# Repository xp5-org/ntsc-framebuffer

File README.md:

NTSC framebuffer built around 74x cmos logic gates and an 128k x 8bit sram module 

** this is incomplete and not yet built, in-progress **

- 8 bits for color + brightness
- 17 bits address
- transfer data in during vblank period

Tasks remaining:
  - complete memory addressing circuitry
  - check gate timings for brightness & color control paths
  - place adjustment potentiometers for setting PNP transistor bias
  - distribute ceramic capacitors
  - add debug testpads onto pcb

# Table of Contents
- [Current PCB Layout](#current-pcb-layout)
- [H&V Counter](#hvcounter)
- [HRESET](#hreset)
- [VRESET](#vreset)
- [HBLANK](#hblank-hsync)
- [VBLANK](#vblank-vsync)
- [COLORBURST](#colorburst)
- [COLORSELECT](#colorselect)
- [BRIGHTNESS](#brightness)
- [MEMORYANDBUS](#memoryandbus)
- [Output Amplifier](#outputamp)
- [Components selection](#components)
- [Simulating](#simtools)

# Current PCB Layout

<br>

<br><br><br><br><br><br><br><br> 

# hvcounter
This is the core of the circuit, its two 4040 counters, one driving the other. the first counts out 454 which is the number of inactive + active horizontal pixels per row. the output is binary, and with enough AND gates alongside numerous D type flipflops, specific events can be timed out and set to form the sync timings needed

<br><br><br><br><br><br><br><br> 

# HRESET

256 + 128 + 64 + 4 + 2
counts out 454 horizontal & sets HRESET flag to high 5V
and on the next clock pulse from not the timer we are resetting but the actual clock source

<br><br><br><br><br><br><br><br> 

# VRESET

vreset is 1V + 4V + 256V for 261 vertical lines before resetting the counter

vertical reset is checked at the end of the horizontal scanline, so we use _HRESET as the clock for vreset - the condition of 261V lines is set only when _HRESET is ready

# HBLANK-HSYNC

the circuit starts off with some DC bias to give a sync tip from the "previous" scanline, and then at H2 + H8 HBLANK-ENABLE flop is cycled on. When this is on, elsewhere in the circuit the bias is cut off and gives us the horizontal sync tip

When H2 + H8 + H32 is seen (H42) , HBLANK_DISABLE is turned on, which is a 2nd flop "HSYNC B"

this lets me chain the hsync events together with explicit start and stop events, block them from re-triggering

<br><br><br><br><br><br><br><br> 

# VBLANK-VSYNC

<br><br><br><br><br><br><br><br> 

# COLORBURST

<br><br><br><br><br><br><br><br> 

# COLORSELECT

the 4-16 mux is often used for memory addressing and is only available in active-low, so in this case im using NOR gates to invert the signal . the MUX outputs are always high-inactive, so all NOR gates except for the active one are getting a positive voltage which turns them all off, exxcept for the active-low received from the MUX, this NOR gate switches on and provides a color clock at specific delays introduced by the 74AHC451's 4-5ns gate propigation delay
<br><br><br><br><br><br><br><br> 

# BRIGHTNESS

<br><br><br><br><br><br><br><br> 

# MEMORYANDBUS

<br><br><br><br><br><br><br><br> 

# outputamp
The output-amplifier interfaces the low-current, low impedience CMOS or TTL logic with the 1.4v, 75-ohm composite. 

HSYNC, Colorburst, and Pixel Input are given to the amplifiers input. Its first passed through a 2n7000 N-channel mosfet which inverts the signal. This drives a PNP transistor to return it back to positive output, this allowed the GND of the composite-out to also be the same reference plane as the GND of this circuit (pnp could be omitted and use only mosfet with resistor network and floating Gnd)

This has two additional mosfets for saturation bias and output voltage reduction (brightness).  The saturation mosfet biases the PNPs turnoff point "upwards" so that its off point rises above what hsync/hblank would have been . this serves the purpose of adding DC bias to reduce the modulation of the output without affecting the output peak (overall brightness). in summary, this is an amplifier which can control the height of the bottoms and tops of the wave output separately. its needed for color, but could dispose of half the mosfets if it were used for monochrome

<br><br><br><br><br><br><br><br> 

# Components
- 74HC74 D-FLOP
- 74HC08 AND
- 74HC02 NOR
- 74hc244 buffers
- 74hc154 4-to-16 mux
- 74ahc541 inv buffers (color delay line)
- CD4040 12 bit counter
- 14.318mhz crystal
- 128x8 sram HM628128DLP-5
- 2n5087 pnp or equivalent
- 2n7000 mosfet
- 7805 regulator

<br><br><br><br><br><br><br><br> 

# simtools

[LTSpice Model of Output Amplifier](./ltspice_sim/video_output_amplifier.asc)

[Digital Logic simulation](./Digital_sim/ntsc_gen.dig)

output amplifier in ltspice, showing peak brightness vs minimum brightness pixels , there is some distortion in the sim. Some gates are switching on/off before others and causing brief voltage spikes, this might be ignorable on the physical circuit ill have to go through the circuit flow to see what the issue is

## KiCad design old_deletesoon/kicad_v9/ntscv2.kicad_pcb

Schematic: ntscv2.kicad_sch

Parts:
C1, C4, C5, C6, C7, C8, C9, C10, C11, C12, C13, C14, C15, C16, C17, C18, C19, C20, C21, C22, C23, C24, C25, C27: C; C_Disc_D5.1mm_W3.2mm_P5.00mm
C2, C3: 10pF; C_Disc_D3.0mm_W2.0mm_P2.50mm
C26: C; C_Radial_D8.0mm_H7.0mm_P3.50mm
D1, D2, D3, D4, D5: 1N4448; D_DO-35_SOD27_P7.62mm_Horizontal
D6, D7, D8, D9, D10, D11, D12, D13, D14, D15, D16, D17, D18, D19, D20, D21, D22, D23, D24, D25, D26, D27, D28, D29, D30, D31, D32, D33, D34, D35, D36: 1N4148; D_DO-35_SOD27_P7.62mm_Horizontal
J1: Conn_Coaxial; BNC_TEConnectivity_1478035_Horizontal
J2: Conn_02x04_Counter_Clockwise; PinSocket_2x04_P2.54mm_Vertical
J3: Conn_02x20_Counter_Clockwise; PinSocket_2x20_P2.54mm_Vertical
Q1: BC327; TO-92_Inline
Q2, Q3, Q4: 2N7000; TO-92_Inline
R1, R3, R4, R5, R6, R7, R8, R9, R10, R11, R12, R13, R14, R15, R16, R17, R18, R19, R20, R21, R22, R23, R24, R25, R26, R27, R28, R29, R30: R; R_Axial_DIN0204_L3.6mm_D1.6mm_P5.08mm_Horizontal
R2: 680; R_Axial_DIN0204_L3.6mm_D1.6mm_P7.62mm_Horizontal
R31, R32, R33: 50R; R_Axial_DIN0204_L3.6mm_D1.6mm_P5.08mm_Horizontal
U1, U2, U3, U4, U5, U40: 74HCT74; SO-14_3.9x8.65mm_P1.27mm
U6, U7, U14, U15: 4040; DIP-16_W7.62mm_SMDSocket_SmallPads
U8: 74HC7014; SOIC-14_3.9x8.7mm_P1.27mm
U9, U10, U11, U13: 4081; DIP-14_W7.62mm
U12: 4081; SO-14_3.9x8.65mm_P1.27mm
U16, U30: 74154; SOIC-24W_7.5x15.4mm_P1.27mm
U17, U18, U21: 74AHC541; SOIC-20W_7.5x12.8mm_P1.27mm
U19, U20, U22, U23: 74HC02; SOIC-14_3.9x8.7mm_P1.27mm
U24, U25, U26, U27, U28, U29, U31, U32: 74HC244; SSOP-20_4.4x6.5mm_P0.65mm
U33: HM628128ALFP-5; DIP-32_W15.24mm; PARTREV 20/6/13
U34, U35: 74HC540D_653; SOIC-20W_7.5x12.8mm_P1.27mm; MPN 74HC540D,653
U46: LM7805_TO220; TO-220-3_Vertical
Y1: Crystal; Crystal_HC49-U_Vertical

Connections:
1H: U6.9 (Q0), U17.2 (A0), U19.2
1V: U7.9 (Q0), U10.1
2H: U6.7 (Q1), U9.1
2V: U7.7 (Q1)
4H: U6.6 (Q2), U9.2
4V: U7.6 (Q2), U10.5
5vdc: C1.1, C4.1, C5.1, C6.1, C7.1, C8.1, C9.1, C10.1, C11.1, C12.1, C13.1, C14.1, C15.1, C16.1, C17.1, C18.1, C19.1, C20.1, C21.1, C22.1, C23.1, C24.1, C25.1, C26.1, J2.1, J2.2, Q1.1 (C), R12.1, U1.10 (~S), U1.13 (~R), U1.14 (VCC), U2.10 (~S), U2.13 (~R), U2.14 (VCC), U3.2 (D), U3.4 (~S), U3.10 (~S), U3.12 (D), U3.14 (VCC), U4.2 (D), U4.4 (~S), U4.10 (~S), U4.12 (D), U4.14 (VCC), U5.2 (D), U5.4 (~S), U5.10 (~S), U5.12 (D), U5.14 (VCC), U6.16 (VDD), U7.16 (VDD), U8.14 (VCC), U9.14 (VDD), U10.14 (VDD), U11.14 (VDD), U12.14 (VDD), U13.14 (VDD), U14.16 (VDD), U15.16 (VDD), U16.24 (VCC), U17.20 (VCC), U18.20 (VCC), U19.14 (VCC), U20.14 (VCC), U21.20 (VCC), U22.14 (VCC), U23.14 (VCC), U24.20 (VCC), U25.20 (VCC), U26.20 (VCC), U27.20 (VCC), U28.20 (VCC), U29.20 (VCC), U30.24 (VCC), U31.20 (VCC), U32.20 (VCC), U33.32 (VCC), U34.20 (VCC), U35.20 (VCC), U40.1 (~R), U40.4 (~S), U40.10 (~S), U40.13 (~R), U40.14 (VCC), U46.3 (VO)
7.1mhz_CLK1: U1.5 (Q), U6.10 (CLK), U7.10 (CLK)
8H: U6.5 (Q3)
8V: U7.5 (Q3)
14mhz_CLK0: U1.3 (C), U2.3 (C), U8.6, U8.8, U8.10
16H: U6.3 (Q4)
16V: U7.3 (Q4)
32H: U6.2 (Q5)
32V: U7.2 (Q5)
64H: U6.4 (Q6), U9.5
64V: U7.4 (Q6)
128H: U6.13 (Q7), U9.6
128V: U7.13 (Q7)
256H: U6.12 (Q8), U9.13
256V: U7.12 (Q8), U10.6
512H: U6.14 (Q9)
512V: U7.14 (Q9)
BIAS_ADJ: J2.8, Q3.2 (G), R5.1
BRIGHTNESS: J2.7, Q4.2 (G), R6.1
CB_DISABLE: U5.9 (Q), U11.5
CB_ENABLE: U5.5 (Q), U12.8
CDL_output_enable: U16.18 (~E0), U16.19 (~E1), U17.1 (G1), U17.19 (G2), U18.1 (G1), U18.19 (G2), U21.1 (G1), U21.19 (G2), U30.18 (~E0), U30.19 (~E1), U34.1 (~OE), U34.19 (~OE2), U35.1 (~OE), U35.19 (~OE2)
FIELDCOUNTER: U40.2 (D), U40.6 (~Q)
GND: C1.2, C2.2, C3.2, C4.2, C5.2, C6.2, C7.2, C8.2, C9.2, C10.2, C11.2, C12.2, C13.2, C14.2, C15.2, C16.2, C17.2, C18.2, C19.2, C20.2, C21.2, C22.2, C23.2, C24.2, C25.2, C26.2, C27.2, J1.2 (Ext), J2.3, J2.4, J2.5, Q2.1 (S), Q3.1 (S), Q4.1 (S), R5.2, R6.2, R7.2, R11.2, R14.2, U1.7 (GND), U2.7 (GND), U3.7 (GND), U4.7 (GND), U5.7 (GND), U6.8 (VSS), U7.8 (VSS), U8.7 (GND), U9.7 (VSS), U10.7 (VSS), U11.7 (VSS), U12.7 (VSS), U13.7 (VSS), U14.8 (VSS), U15.8 (VSS), U16.12 (GND), U17.10 (GND), U18.10 (GND), U19.7 (GND), U20.7 (GND), U21.10 (GND), U22.7 (GND), U23.7 (GND), U24.10 (GND), U25.10 (GND), U26.10 (GND), U27.10 (GND), U28.10 (GND), U29.10 (GND), U30.12 (GND), U31.10 (GND), U32.10 (GND), U33.16 (VSS), U34.10 (GND), U35.10 (GND), U40.7 (GND), U46.2 (GND)
H2: U10.8, U11.12, U12.6
H4: U12.9
H8: U10.9, U11.6, U11.8
H16: U12.1
H32: U11.9, U12.2
H64: U12.13
HRESET: U2.5 (Q), U6.11 (Reset)
HSYNCA: U3.5 (Q)
HSYNCB: D2.2 (A), U3.9 (Q), U13.9
unnamed: C2.1, U8.1, Y1.1
unnamed: C3.1, R2.2, Y1.2
unnamed: D1.1 (K), U10.12
unnamed: D2.1 (K), U10.13
unnamed: D3.2 (A), U10.11
unnamed: D3.1 (K), R1.1
unnamed: D4.2 (A), U13.4
unnamed: D4.1 (K), R3.1
unnamed: D5.2 (A), U13.11
unnamed: D5.1 (K), R4.1
unnamed: D6.2 (A), U19.1
unnamed: D7.2 (A), U19.4
unnamed: D8.2 (A), U19.10
unnamed: D9.2 (A), U19.13
unnamed: D10.2 (A), U20.1
unnamed: D11.2 (A), U20.4
unnamed: D12.2 (A), U20.10
unnamed: D13.2 (A), U20.13
unnamed: D14.2 (A), U22.1
unnamed: D15.2 (A), U22.4
unnamed: D16.2 (A), U22.10
unnamed: D17.2 (A), U22.13
unnamed: D18.2 (A), U23.1
unnamed: D19.2 (A), U23.4
unnamed: D20.2 (A), U23.10
unnamed: D21.2 (A), R15.2
unnamed: D22.2 (A), R16.2
unnamed: D23.2 (A), R17.2
unnamed: D24.2 (A), R18.2
unnamed: D25.2 (A), R19.2
unnamed: D26.2 (A), R20.2
unnamed: D27.2 (A), R21.2
unnamed: D28.2 (A), R22.2
unnamed: D29.2 (A), R23.2
unnamed: D30.2 (A), R24.2
unnamed: D31.2 (A), R25.2
unnamed: D32.2 (A), R26.2
unnamed: D33.2 (A), R27.2
unnamed: D34.2 (A), R28.2
unnamed: D35.2 (A), R29.2
unnamed: D36.2 (A), R30.2
unnamed: Q1.2 (B), R9.2
unnamed: Q1.3 (E), R10.1
unnamed: Q2.3 (D), R8.2
unnamed: Q3.3 (D), R8.1, R9.1, R12.2, R14.1
unnamed: Q4.3 (D), R13.2
unnamed: R2.1, U8.2, U8.3
unnamed: U1.2 (D), U1.6 (~Q)
unnamed: U1.1 (~R), U1.4 (~S)
unnamed: U1.11 (C), U13.3
unnamed: U1.8 (~Q), U1.12 (D)
unnamed: U2.2 (D), U9.11
unnamed: U2.1 (~R), U2.4 (~S)
unnamed: U2.12 (D), U10.3
unnamed: U3.3 (C), U10.10
unnamed: U3.11 (C), U11.11
unnamed: U4.3 (C), U11.3
unnamed: U5.3 (C), U12.4
unnamed: U5.11 (C), U12.11
unnamed: U8.4, U8.5, U8.9, U8.11
unnamed: U9.3, U9.8
unnamed: U9.4, U9.9
unnamed: U9.10, U9.12
unnamed: U10.2, U10.4
unnamed: U11.2, U11.4
unnamed: U11.10, U11.13
unnamed: U12.3, U12.5
unnamed: U12.10, U12.12
unnamed: U13.10, U13.13
unnamed: U17.3 (A1), U17.18 (Y0)
unnamed: U17.4 (A2), U17.17 (Y1)
unnamed: U17.5 (A3), U17.16 (Y2)
unnamed: U17.6 (A4), U17.15 (Y3)
unnamed: U17.7 (A5), U17.14 (Y4)
unnamed: U17.8 (A6), U17.13 (Y5)
unnamed: U17.9 (A7), U17.12 (Y6)
unnamed: U17.11 (Y7), U18.9 (A7)
unnamed: U18.2 (A0), U18.17 (Y1)
unnamed: U18.3 (A1), U18.16 (Y2)
unnamed: U18.4 (A2), U18.15 (Y3)
unnamed: U18.5 (A3), U18.14 (Y4)
unnamed: U18.6 (A4), U18.13 (Y5)
unnamed: U18.7 (A5), U18.12 (Y6)
unnamed: U18.8 (A6), U18.11 (Y7)
unnamed: U18.18 (Y0), U21.2 (A0)
unnamed: U21.3 (A1), U21.18 (Y0)
unnamed: U21.4 (A2), U21.17 (Y1)
unnamed: U21.5 (A3), U21.16 (Y2)
unnamed: U21.6 (A4), U21.15 (Y3)
unnamed: U21.7 (A5), U21.14 (Y4)
unnamed: U21.8 (A6), U21.13 (Y5)
unnamed: U21.9 (A7), U21.12 (Y6)
unnamed: R15.1, U34.18 (~Y0)
unnamed: R19.1, U34.17 (~Y1)
unnamed: R23.1, U34.16 (~Y2)
unnamed: R27.1, U34.15 (~Y3)
unnamed: R16.1, U34.14 (~Y4)
unnamed: R20.1, U34.13 (~Y5)
unnamed: R24.1, U34.12 (~Y6)
unnamed: R28.1, U34.11 (~Y7)
unnamed: R17.1, U35.18 (~Y0)
unnamed: R21.1, U35.17 (~Y1)
unnamed: R25.1, U35.16 (~Y2)
unnamed: R29.1, U35.15 (~Y3)
unnamed: R18.1, U35.14 (~Y4)
unnamed: R22.1, U35.13 (~Y5)
unnamed: R26.1, U35.12 (~Y6)
unnamed: R30.1, U35.11 (~Y7)
unnamed: U40.5 (Q), U40.11 (C)
Output_Signal_75ohm: J1.1 (In), R10.2, R11.1, R13.1
PAGECOUNTER: U40.8 (~Q), U40.12 (D)
PIXELDRAWEN: U4.5 (Q), U13.6
PIXEL_INPUT_FROM_COLORARRAY: U13.5
V16: U4.11 (C)
VBLANK: R32.2, U4.9 (Q)
VRESET: U2.9 (Q), U7.11 (Reset), U14.11 (Reset), U15.11 (Reset), U40.3 (C)
_CB_DISABLE: U5.8 (~Q)
_CB_ENABLE: U5.6 (~Q)
_HRESET: U2.6 (~Q), U2.8 (~Q), U2.11 (C), U3.1 (~R), U3.13 (~R), U4.1 (~R), U5.1 (~R), U5.13 (~R)
_HSYNCA: D1.2 (A), U3.6 (~Q), U13.8
_HSYNCB: U3.8 (~Q)
_PIXELDRAWEN: U4.6 (~Q)
_VBLANK: R31.1, R33.2, U4.8 (~Q), U11.1, U13.2
_VRESET: U4.13 (~R)
ampinput: J2.6, Q2.2 (G), R1.2, R3.2, R4.2, R7.1
bus_addr0: J3.40, U29.11 (2A3)
bus_addr1: J3.39, U27.2 (1A0)
bus_addr2: J3.38, U27.4 (1A1)
bus_addr3: J3.37, U27.6 (1A2)
bus_addr4: J3.36, U27.8 (1A3)
bus_addr5: J3.35, U27.17 (2A0)
bus_addr6: J3.34, U27.15 (2A1)
bus_addr7: J3.33, U27.13 (2A2)
bus_addr8: J3.32, U27.11 (2A3)
bus_addr9: J3.31, U28.2 (1A0)
bus_addr10: J3.30, U28.4 (1A1)
bus_addr11: J3.29, U28.6 (1A2)
bus_addr12: J3.28, U28.8 (1A3)
bus_addr13: J3.27, U28.17 (2A0)
bus_addr14: J3.26, U28.15 (2A1)
bus_addr15: J3.25, U28.13 (2A2)
bus_addr16: J3.24, U28.11 (2A3)
bus_data0: J3.1, U31.2 (1A0)
bus_data1: J3.2, U31.4 (1A1)
bus_data2: J3.3, U31.6 (1A2)
bus_data3: J3.4, U31.8 (1A3)
bus_data4: J3.5, U31.17 (2A0)
bus_data5: J3.6, U31.15 (2A1)
bus_data6: J3.7, U31.13 (2A2)
bus_data7: J3.8, U31.11 (2A3)
bus_writeflag_9thbit: J3.9, R31.2, U13.1, U29.13 (2A2)
colorburst_delayline: D7.1 (K), D8.1 (K), D9.1 (K), D10.1 (K), D11.1 (K), D12.1 (K), D13.1 (K), D14.1 (K), D15.1 (K), D16.1 (K), D17.1 (K), D18.1 (K), D19.1 (K), D20.1 (K); also elsewhere on the board
colorburst_ref_colorwhite: D6.1 (K), U13.12
colordata_0: U16.23 (A0), U32.2 (1A0)
colordata_1: U16.22 (A1), U32.4 (1A1)
colordata_2: U16.21 (A2), U32.6 (1A2)
colordata_3: U16.20 (A3), U32.8 (1A3)
colordata_4: U30.23 (A0), U32.17 (2A0)
colordata_5: U30.22 (A1), U32.15 (2A1)
colordata_6: U30.21 (A2), U32.13 (2A2)
colordata_7: U30.20 (A3), U32.11 (2A3)
colorselect1: U16.1 (~S0), U19.3
colorselect2: U16.2 (~S1), U19.6
colorselect3: U16.3 (~S2), U19.9
colorselect4: U16.4 (~S3), U19.12
colorselect5: U16.5 (~S4), U20.3
colorselect6: U16.6 (~S5), U20.6
colorselect7: U16.7 (~S6), U20.9
colorselect8: U16.8 (~S7), U20.12
colorselect9: U16.9 (~S8), U22.3
colorselect10: U16.10 (~S9), U22.6
colorselect11: U16.11 (~S10), U22.9
colorselect12: U16.13 (~S11), U22.12
colorselect13: U16.14 (~S12), U23.3
colorselect14: U16.15 (~S13), U23.6
colorselect15: U16.16 (~S14), U23.9
colorselect16: U16.17 (~S15)
delayline2: U19.5
delayline3: U19.8
delayline4: U19.11
delayline5: U20.2
delayline6: U20.5
delayline7: U20.8
delayline8: U20.11
delayline9: U22.2
delayline10: U22.5
delayline11: U22.8
delayline12: U22.11
delayline13: U23.2
delayline14: U23.5
delayline15: U23.8
ext_bustoggle: R33.1, U27.1 (1OE), U27.19 (2OE), U28.1 (1OE), U28.19 (2OE), U29.1 (1OE), U29.19 (2OE), U31.1 (1OE), U31.19 (2OE)
inputvoltage: C27.1, U46.1 (VI)
int_bustoggle: R32.1, U24.1 (1OE), U24.19 (2OE), U25.1 (1OE), U25.19 (2OE), U26.1 (1OE), U26.19 (2OE), U32.1 (1OE), U32.19 (2OE)
luminosity_select1: U30.1 (~S0), U34.2 (A0)
luminosity_select2: U30.2 (~S1), U34.3 (A1)
luminosity_select3: U30.3 (~S2), U34.4 (A2)
luminosity_select4: U30.4 (~S3), U34.5 (A3)
luminosity_select5: U30.5 (~S4), U34.6 (A4)
luminosity_select6: U30.6 (~S5), U34.7 (A5)
luminosity_select7: U30.7 (~S6), U34.8 (A6)
luminosity_select8: U30.8 (~S7), U34.9 (A7)
luminosity_select9: U30.9 (~S8), U35.2 (A0)
luminosity_select10: U30.10 (~S9), U35.3 (A1)
luminosity_select11: U30.11 (~S10), U35.4 (A2)
luminosity_select12: U30.13 (~S11), U35.5 (A3)
luminosity_select13: U30.14 (~S12), U35.6 (A4)
luminosity_select14: U30.15 (~S13), U35.7 (A5)
luminosity_select15: U30.16 (~S14), U35.8 (A6)
luminosity_select16: U30.17 (~S15), U35.9 (A7)
m1_data0: U31.18 (1Y0), U32.18 (1Y0), U33.13 (I/O0)
m1_data1: U31.16 (1Y1), U32.16 (1Y1), U33.14 (I/O1)
m1_data2: U31.14 (1Y2), U32.14 (1Y2), U33.15 (I/O2)
m1_data3: U31.12 (1Y3), U32.12 (1Y3), U33.17 (I/O3)
m1_data4: U31.3 (2Y0), U32.3 (2Y0), U33.18 (I/O4)
m1_data5: U31.5 (2Y1), U32.5 (2Y1), U33.19 (I/O5)
m1_data6: U31.7 (2Y2), U32.7 (2Y2), U33.20 (I/O6)
m1_data7: U31.9 (2Y3), U32.9 (2Y3), U33.21 (I/O7)
m_addr0: U14.9 (Q0), U26.11 (2A3)
m_addr1: U14.7 (Q1), U24.2 (1A0)
m_addr2: U14.6 (Q2), U24.4 (1A1)
m_addr3: U14.5 (Q3), U24.6 (1A2)
m_addr4: U14.3 (Q4), U24.8 (1A3)
m_addr5: U14.2 (Q5), U24.17 (2A0)
m_addr6: U14.4 (Q6), U24.15 (2A1)
m_addr7: U14.13 (Q7), U24.13 (2A2)
m_addr8: U14.12 (Q8), U24.11 (2A3)
m_addr9: U14.14 (Q9), U25.2 (1A0)
m_addr10: U14.15 (Q10), U25.4 (1A1)
m_addr11: U14.1 (Q11), U15.10 (CLK), U25.6 (1A2)
m_addr12: U15.9 (Q0), U25.8 (1A3)
m_addr13: U15.7 (Q1), U25.17 (2A0)
m_addr14: U15.6 (Q2), U25.15 (2A1)
m_addr15: U15.5 (Q3), U25.13 (2A2)
m_addr16: U15.3 (Q4), U25.11 (2A3)
m_addr17: U15.2 (Q5)
m_addr18: U15.4 (Q6)
m_addr19: U15.13 (Q7)
m_addr20: U15.12 (Q8)
m_addr21: U15.14 (Q9)
m_addr22: U15.15 (Q10)
m_addr23: U15.1 (Q11)
output_clamp: D21.1 (K), D22.1 (K), D23.1 (K), D24.1 (K), D25.1 (K), D26.1 (K), D27.1 (K), D28.1 (K), D29.1 (K), D30.1 (K), D31.1 (K), D32.1 (K), D33.1 (K), D34.1 (K), D35.1 (K), D36.1 (K)
readwrite_toggle_flag: U1.9 (Q)
sram1_addr0: U26.9 (2Y3), U29.9 (2Y3), U33.12 (A0)
sram1_addr1: U24.18 (1Y0), U27.18 (1Y0), U33.11 (A1)
sram1_addr2: U24.16 (1Y1), U27.16 (1Y1), U33.10 (A2)
sram1_addr3: U24.14 (1Y2), U27.14 (1Y2), U33.9 (A3)
sram1_addr4: U24.12 (1Y3), U27.12 (1Y3), U33.8 (A4)
sram1_addr5: U24.3 (2Y0), U27.3 (2Y0), U33.7 (A5)
sram1_addr6: U24.5 (2Y1), U27.5 (2Y1), U33.6 (A6)
sram1_addr7: U24.7 (2Y2), U27.7 (2Y2), U33.5 (A7)
sram1_addr8: U24.9 (2Y3), U27.9 (2Y3), U33.27 (A8)
sram1_addr9: U25.18 (1Y0), U28.18 (1Y0), U33.26 (A9)
sram1_addr10: U25.16 (1Y1), U28.16 (1Y1), U33.23 (A10)
sram1_addr11: U25.14 (1Y2), U28.14 (1Y2), U33.25 (A11)
sram1_addr12: U25.12 (1Y3), U28.12 (1Y3), U33.4 (A12)
sram1_addr13: U25.3 (2Y0), U28.3 (2Y0), U33.28 (A13)
sram1_addr14: U25.5 (2Y1), U28.5 (2Y1), U33.3 (A14)
sram1_addr15: U25.7 (2Y2), U28.7 (2Y2), U33.31 (A15)
sram1_addr16: U25.9 (2Y3), U28.9 (2Y3), U33.2 (A16)
write_ready9thbit: U29.7 (2Y2)

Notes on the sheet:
Bus interrupt
pagecounter is unneeded for 1 chip but its already in the package
14.318Mhz clock gen
pull the int flag low when in use video side has priority
non-inverting required here
Bus Connection
BRIGHTNESS
with using 1 ram chip, VBLANK is the same thing as "interrupt" once the first 16 lines are counted out, vblank turns off memory must be available to read this same flag flips the buffers
HSYNC input
2 bit counter for A or B mem bank switching 1 frame = 2 vresets / 2 ntsc fields counts out 2 frames / 4 fields
Color Delay Line
Horizontal Blank Enable
white color pixel same phase as colorburst source
Vertical Reset
read-from-bus
notes
74HC154 & 74ACH541 - pull both E0 & E1 low to enable output hold H to disable output
PIXEL input
brightness select
Horizontal reset
Memory bank A
Pixel Drive Enable
color black = turn off pixel input 74x154 is active-low
Horizontal & Vertical Line Counter
COLORBURST input
if this were dual buffered / dual ram chip - connect bus_interrupt_flag to the field/page counter
Colorburst Disable
Colorburst Enable
Memory Address Counter
ignore the bus flag if _vblank switches off
can be upgraded to 6x CD74HC190 for preset/preload gives ability to draw sprites
BIAS
Horizontal Blank Disable
Output Amplifier
toggle memory-to-bus connection
need some way to indicate the bus was updated without clock control signals
Vertical Blank

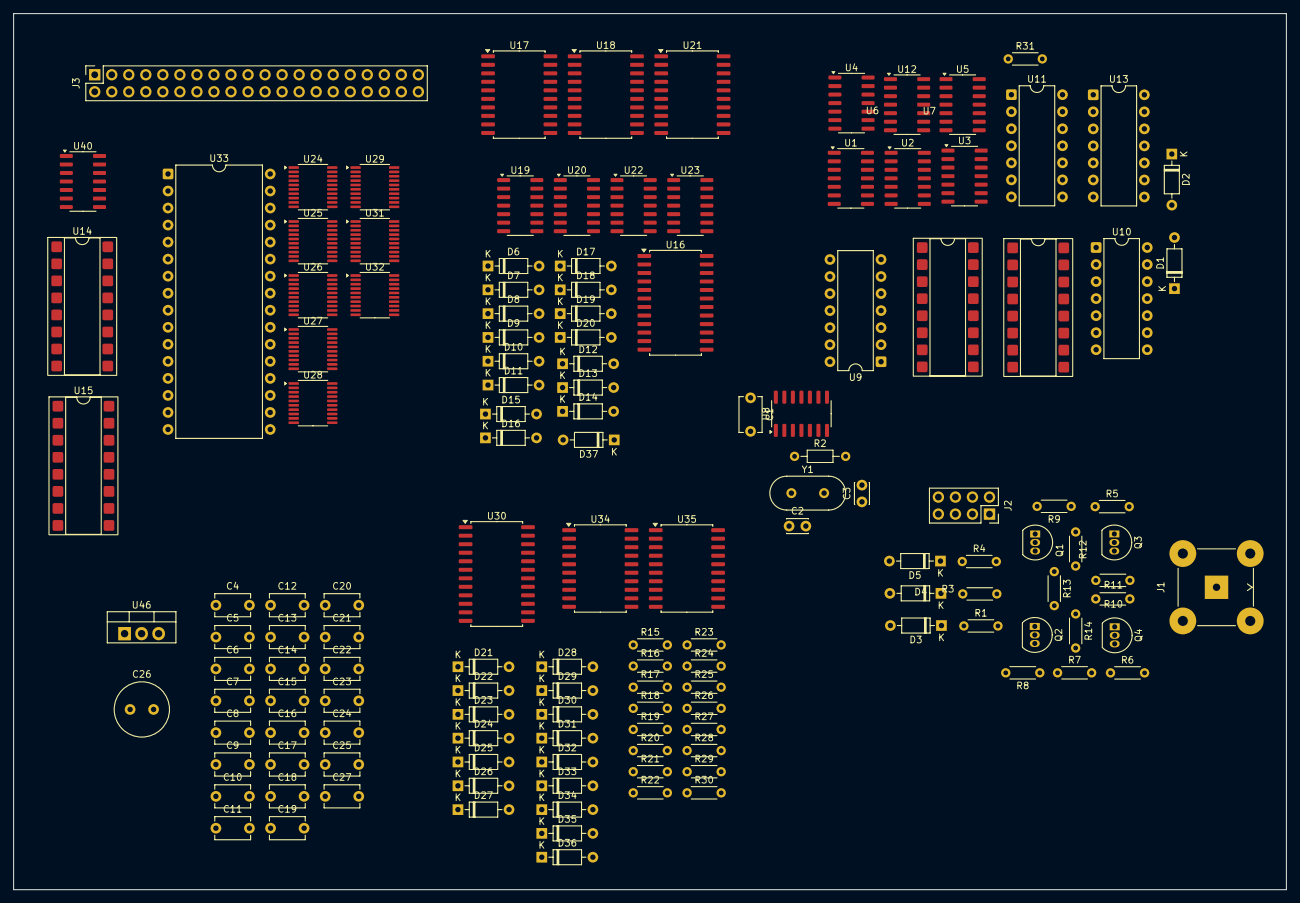
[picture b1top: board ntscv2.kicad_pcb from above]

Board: 2 copper layers, 189.8 x 130.6 mm, 140 parts (0 on the bottom side), 254 nets, no tracks yet.

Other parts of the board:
D37: 1N4148; D_DO-35_SOD27_P7.62mm_Horizontal

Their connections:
colorburst_delayline: D37.1 (K); also elsewhere on the board

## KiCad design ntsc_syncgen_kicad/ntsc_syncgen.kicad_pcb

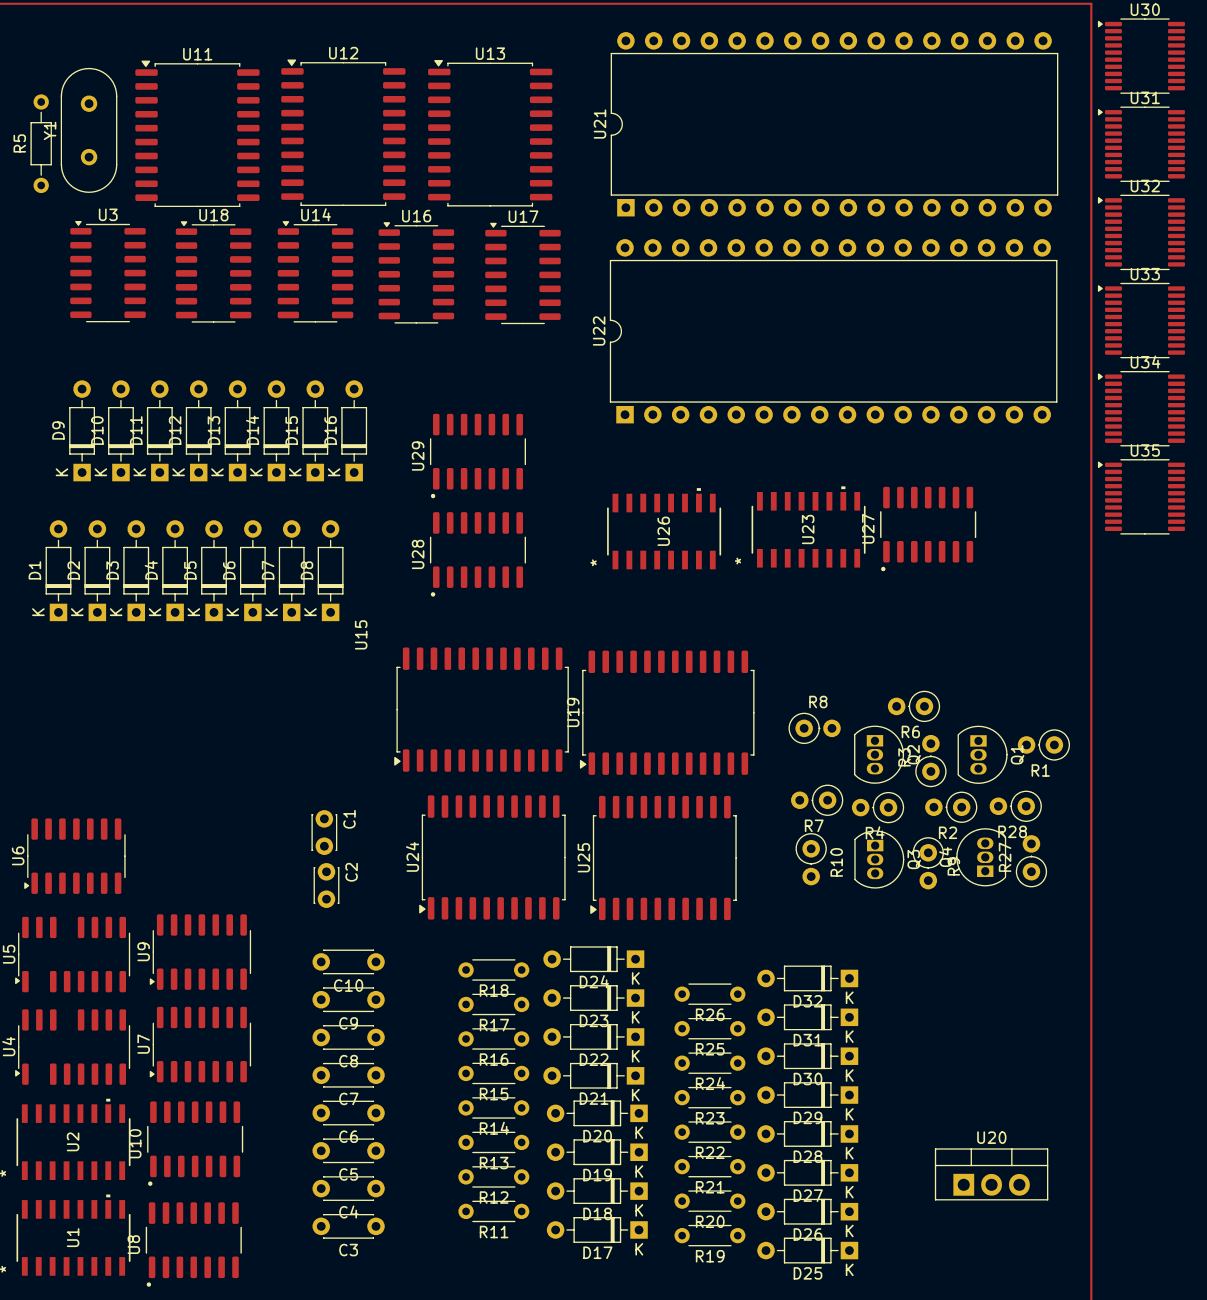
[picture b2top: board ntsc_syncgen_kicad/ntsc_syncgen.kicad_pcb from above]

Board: 2 copper layers, 110 parts (0 on the bottom side), 175 nets, no tracks yet.

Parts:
C1, C2: 10pF; C_Disc_D3.0mm_W2.0mm_P2.50mm
C3, C4, C5, C6, C7, C8, C9, C10: C; C_Disc_D4.3mm_W1.9mm_P5.00mm
D1, D2, D3, D4, D5, D6, D7, D8, D9, D10, D11, D12, D13, D14, D15, D16, D17, D18, D19, D20, D21, D22, D23, D24, D25, D26, D27, D28, D29, D30, D31, D32: 1N4148; D_DO-35_SOD27_P7.62mm_Horizontal
Q1, Q3, Q4: 2N7000; TO-92_Inline
Q2: BC212; TO-92_Inline
R1, R27: 600R; R_Axial_DIN0207_L6.3mm_D2.5mm_P2.54mm_Vertical
R2: 30R; R_Axial_DIN0207_L6.3mm_D2.5mm_P2.54mm_Vertical
R3: 40R; R_Axial_DIN0207_L6.3mm_D2.5mm_P2.54mm_Vertical
R4: 400R; R_Axial_DIN0207_L6.3mm_D2.5mm_P2.54mm_Vertical
R5: 680; R_Axial_DIN0204_L3.6mm_D1.6mm_P7.62mm_Horizontal
R6: 70R; R_Axial_DIN0207_L6.3mm_D2.5mm_P2.54mm_Vertical
R7: 140R; R_Axial_DIN0207_L6.3mm_D2.5mm_P2.54mm_Vertical
R8: 75R; R_Axial_DIN0207_L6.3mm_D2.5mm_P2.54mm_Vertical
R9: 800R; R_Axial_DIN0207_L6.3mm_D2.5mm_P2.54mm_Vertical
R10: 15R; R_Axial_DIN0207_L6.3mm_D2.5mm_P2.54mm_Vertical
R11, R12, R13, R14, R15, R16, R17, R18, R19, R20, R21, R22, R23, R24, R25, R26: R; R_Axial_DIN0204_L3.6mm_D1.6mm_P5.08mm_Horizontal
R28: 35R; R_Axial_DIN0207_L6.3mm_D2.5mm_P2.54mm_Vertical
U1, U2, U23, U26: 74HC4040D; SOT109-1_NXP
U3: 74HC7014; SOIC-14_3.9x8.7mm_P1.27mm
U4, U5: 74HC00; SOIC-14-16_3.9x9.9mm_P1.27mm
U6: 74HC00; SOIC-14_3.9x8.7mm_P1.27mm
U7: 4081; SOIC-14_3.9x8.7mm_P1.27mm
U8, U10, U27, U28, U29: 74HC74; SOIC127P600X175-14N
U9: 4001; SOIC-14_3.9x8.7mm_P1.27mm
U11, U12, U13: 74AHC541; SOIC-20W_7.5x12.8mm_P1.27mm
U14, U16, U17, U18: 74HC02; SOIC-14_3.9x8.7mm_P1.27mm
U15, U19: 74154; SOIC-24W_7.5x15.4mm_P1.27mm
U20: LM7805_TO220; TO-220-3_Vertical
U21, U22: HM628128ALFP-5; DIP-32_W15.24mm
U24, U25: 74HC540D_653; SOIC-20W_7.5x12.8mm_P1.27mm
U30, U31, U32, U33, U34, U35: 74HC244; SSOP-20_4.4x6.5mm_P0.65mm
Y1: Crystal; Crystal_HC49-U_Vertical

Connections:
1H: U2.9 (Q0), U11.2 (A0), U14.2
1V: U1.9 (Q0), U6.5
2H: U2.7 (Q1), U7.1
4H: U2.6 (Q2), U7.2
4V: U1.6 (Q2), U4.10, U6.2
7.1mhz_CLK1: U2.10 (CP*), U8.5 (Q), U10.3 (C), U27.3 (C)
8V: U1.5 (Q3), U4.4, U4.5
16H: U2.3 (Q4), U5.1
16V: U1.3 (Q4), U9.13
64H: U2.4 (Q6), U7.5
128H: U2.13 (Q7), U7.6
256H: U2.12 (Q8), U7.13
256V: U1.12 (Q8), U6.1
COMPOSITE_OUT: R7.2, R8.1, R10.1
GND: C1.2, C2.2, C3.2, C4.2, C5.2, C6.2, C7.2, C8.2, C9.2, C10.2, Q1.1 (S), Q3.1 (S), Q4.1 (S), R1.1, R4.2, R8.2, R9.1, R27.1, U1.8 (GND), U2.8 (GND), U3.7 (GND), U4.7 (GND), U5.7 (GND), U6.7 (GND), U7.7 (VSS), U8.7 (GND), U9.7 (VSS), U10.7 (GND), U11.10 (GND), U12.10 (GND), U13.10 (GND), U20.2 (GND), U23.8 (GND), U26.8 (GND)
HRESET: U1.10 (CP*), U2.11 (MR), U10.6 (~Q), U10.11 (C)
unnamed: C1.1, U3.1, Y1.1
unnamed: C2.1, R5.2, Y1.2
unnamed: D1.2 (A), U14.1
unnamed: D2.2 (A), U14.4
unnamed: D3.2 (A), U14.10
unnamed: D4.2 (A), U14.13
unnamed: D5.2 (A), U16.1
unnamed: D6.2 (A), U16.4
unnamed: D7.2 (A), U16.10
unnamed: D8.2 (A), U17.1
unnamed: D9.2 (A), U17.4
unnamed: D10.2 (A), U17.10
unnamed: D11.2 (A), U17.13
unnamed: D12.2 (A), U18.1
unnamed: D13.2 (A), U18.4
unnamed: D14.2 (A), U18.10
unnamed: D15.2 (A), U18.13
unnamed: D16.2 (A), U16.13
unnamed: D17.2 (A), R11.2
unnamed: D18.2 (A), R12.2
unnamed: D19.2 (A), R13.2
unnamed: D20.2 (A), R14.2
unnamed: D21.2 (A), R16.2
unnamed: D22.2 (A), R17.2
unnamed: D23.2 (A), R18.2
unnamed: D24.2 (A), R15.2
unnamed: D25.2 (A), R19.2
unnamed: D26.2 (A), R20.2
unnamed: D27.2 (A), R21.2
unnamed: D28.2 (A), R22.2
unnamed: D29.2 (A), R23.2
unnamed: D30.2 (A), R24.2
unnamed: D31.2 (A), R25.2
unnamed: D32.2 (A), R26.2
unnamed: Q1.3 (D), R3.2
unnamed: Q2.2 (B), R6.2
unnamed: Q2.3 (E), R7.1
unnamed: Q3.3 (D), R10.2
unnamed: Q4.3 (D), R28.1
unnamed: R2.2, R3.1, R4.1, R6.1, R28.2
unnamed: R5.1, U3.2, U3.3
unnamed: U4.3, U4.9
unnamed: U5.3, U5.9
unnamed: U5.6, U5.10, U5.12
unnamed: U6.3, U6.4
unnamed: U7.3, U7.8
unnamed: U7.9, U7.11
unnamed: U7.4, U7.12
unnamed: U3.4, U8.3 (C)
unnamed: U8.2 (D), U8.6 (~Q)
unnamed: U7.10, U10.2 (D)
unnamed: U6.6, U10.12 (D)
unnamed: U11.3 (A1), U11.18 (Y0)
unnamed: U11.4 (A2), U11.17 (Y1)
unnamed: U11.5 (A3), U11.16 (Y2)
unnamed: U11.6 (A4), U11.15 (Y3)
unnamed: U11.7 (A5), U11.14 (Y4)
unnamed: U11.8 (A6), U11.13 (Y5)
unnamed: U11.9 (A7), U11.12 (Y6)
unnamed: U11.1 (G1), U11.19 (G2)
unnamed: U11.11 (Y7), U12.9 (A7)
unnamed: U12.2 (A0), U12.17 (Y1)
unnamed: U12.3 (A1), U12.16 (Y2)
unnamed: U12.4 (A2), U12.15 (Y3)
unnamed: U12.5 (A3), U12.14 (Y4)
unnamed: U12.6 (A4), U12.13 (Y5)
unnamed: U12.7 (A5), U12.12 (Y6)
unnamed: U12.8 (A6), U12.11 (Y7)
unnamed: U12.1 (G1), U12.19 (G2)
unnamed: U12.18 (Y0), U13.2 (A0)
unnamed: U13.3 (A1), U13.18 (Y0)
unnamed: U13.4 (A2), U13.17 (Y1)
unnamed: U13.5 (A3), U13.16 (Y2)
unnamed: U13.6 (A4), U13.15 (Y3)
unnamed: U13.7 (A5), U13.14 (Y4)
unnamed: U13.8 (A6), U13.13 (Y5)
unnamed: U13.9 (A7), U13.12 (Y6)
unnamed: U13.1 (G1), U13.19 (G2)
unnamed: R11.1, U24.18 (~Y0)
unnamed: R12.1, U24.17 (~Y1)
unnamed: R13.1, U24.16 (~Y2)
unnamed: R14.1, U24.15 (~Y3)
unnamed: R16.1, U24.14 (~Y4)
unnamed: R17.1, U24.13 (~Y5)
unnamed: R18.1, U24.12 (~Y6)
unnamed: R15.1, U24.11 (~Y7)
unnamed: R19.1, U25.18 (~Y0)
unnamed: R21.1, U25.17 (~Y1)
unnamed: R23.1, U25.16 (~Y2)
unnamed: R25.1, U25.15 (~Y3)
unnamed: R20.1, U25.14 (~Y4)
unnamed: R22.1, U25.13 (~Y5)
unnamed: R24.1, U25.12 (~Y6)
unnamed: R26.1, U25.11 (~Y7)
unnamed: U27.2 (D), U27.6 (~Q)
unnamed: U28.2 (D), U28.6 (~Q)
unnamed: U28.5 (Q), U29.3 (C)
VBLANK: U4.1, U9.9, U9.11
VCC: C3.1, C4.1, C5.1, C6.1, C7.1, C8.1, C9.1, C10.1, Q2.1 (C), R2.1, U1.16 (VCC), U2.16 (VCC), U3.14 (VCC), U4.14 (VCC), U5.14 (VCC), U6.14 (VCC), U7.14 (VDD), U8.1 (~R), U8.4 (~S), U8.14 (VCC), U9.14 (VDD), U10.1 (~R), U10.4 (~S), U10.10 (~S), U10.13 (~R), U10.14 (VCC), U11.20 (VCC), U12.20 (VCC), U13.20 (VCC), U18.11, U20.3 (VO), U23.16 (VCC), U26.16 (VCC), U27.1 (~R), U27.4 (~S), U28.1 (~R), U28.4 (~S), U29.1 (~R), U29.4 (~S)
VRESET: U1.11 (MR), U9.8, U10.8 (~Q), U28.3 (C)
_HBLANK: U5.8, U9.5
_HRESET: U5.5, U10.5 (Q)
_VBLANK: U9.6, U9.10, U9.12
_VRESET: U10.9 (Q), U23.11 (MR), U26.11 (MR)
_fieldcounter: U29.2 (D), U29.6 (~Q)
bias_input: Q4.2 (G), R27.2
colorburst_delayline: D1.1 (K), D2.1 (K), D3.1 (K), D4.1 (K), D5.1 (K), D6.1 (K), D7.1 (K), D8.1 (K), D9.1 (K), D10.1 (K), D11.1 (K), D12.1 (K), D13.1 (K), D14.1 (K), D15.1 (K), D16.1 (K)
colorselect1: U14.3, U15.1 (~S0)
colorselect2: U14.6, U15.2 (~S1)
colorselect3: U14.9, U15.3 (~S2)
colorselect4: U14.12, U15.4 (~S3)
colorselect5: U15.5 (~S4), U16.3
colorselect6: U15.6 (~S5), U16.6
colorselect7: U15.7 (~S6), U16.9
colorselect8: U15.8 (~S7), U16.12
colorselect9: U15.9 (~S8), U17.3
colorselect10: U15.10 (~S9), U17.6
colorselect11: U15.11 (~S10), U17.9
colorselect12: U15.13 (~S11), U17.12
colorselect13: U15.14 (~S12), U18.3
colorselect14: U15.15 (~S13), U18.6
colorselect15: U15.16 (~S14), U18.9
colorselect16: U15.17 (~S15), U18.12
luminosity_select1: U19.1 (~S0), U24.2 (A0)
luminosity_select2: U19.2 (~S1), U24.3 (A1)
luminosity_select3: U19.3 (~S2), U24.4 (A2)
luminosity_select4: U19.4 (~S3), U24.5 (A3)
luminosity_select5: U19.5 (~S4), U24.6 (A4)
luminosity_select6: U19.6 (~S5), U24.7 (A5)
luminosity_select7: U19.7 (~S6), U24.8 (A6)
luminosity_select8: U19.8 (~S7), U24.9 (A7)
luminosity_select9: U19.9 (~S8), U25.2 (A0)
luminosity_select10: U19.10 (~S9), U25.3 (A1)
luminosity_select11: U19.11 (~S10), U25.4 (A2)
luminosity_select12: U19.13 (~S11), U25.5 (A3)
luminosity_select13: U19.14 (~S12), U25.6 (A4)
luminosity_select14: U19.15 (~S13), U25.7 (A5)
luminosity_select15: U19.16 (~S14), U25.8 (A6)
luminosity_select16: U19.17 (~S15), U25.9 (A7)
m_addr0: U26.9 (Q0), U30.11 (2A3), U31.11 (2A3)
m_addr1: U26.7 (Q1), U33.2 (1A0), U34.2 (1A0)
m_addr2: U26.6 (Q2), U33.4 (1A1), U34.4 (1A1)
m_addr3: U26.5 (Q3), U33.6 (1A2), U34.6 (1A2)
m_addr4: U26.3 (Q4), U33.8 (1A3), U34.8 (1A3)
m_addr5: U26.2 (Q5), U33.17 (2A0), U34.17 (2A0)
m_addr6: U26.4 (Q6), U33.15 (2A1), U34.15 (2A1)
m_addr7: U26.13 (Q7), U33.13 (2A2), U34.13 (2A2)
m_addr8: U26.12 (Q8), U33.11 (2A3), U34.11 (2A3)
m_addr9: U26.14 (Q9), U32.2 (1A0), U35.2 (1A0)
m_addr10: U26.15 (Q10), U32.4 (1A1), U35.4 (1A1)
m_addr11: U23.10 (CP*), U26.1 (Q11), U32.6 (1A2), U35.6 (1A2)
m_addr12: U23.7 (Q1), U32.8 (1A3), U35.8 (1A3)
m_addr13: U23.6 (Q2), U32.17 (2A0), U35.17 (2A0)
m_addr14: U23.5 (Q3), U32.15 (2A1), U35.15 (2A1)
m_addr15: U23.3 (Q4), U32.13 (2A2), U35.13 (2A2)
m_addr16: U23.2 (Q5), U32.11 (2A3), U35.11 (2A3)
output_clamp: Q3.2 (G), R9.2
ramclock: U26.10 (CP*), U27.5 (Q)
video_amplifier_input: Q1.2 (G), R1.2

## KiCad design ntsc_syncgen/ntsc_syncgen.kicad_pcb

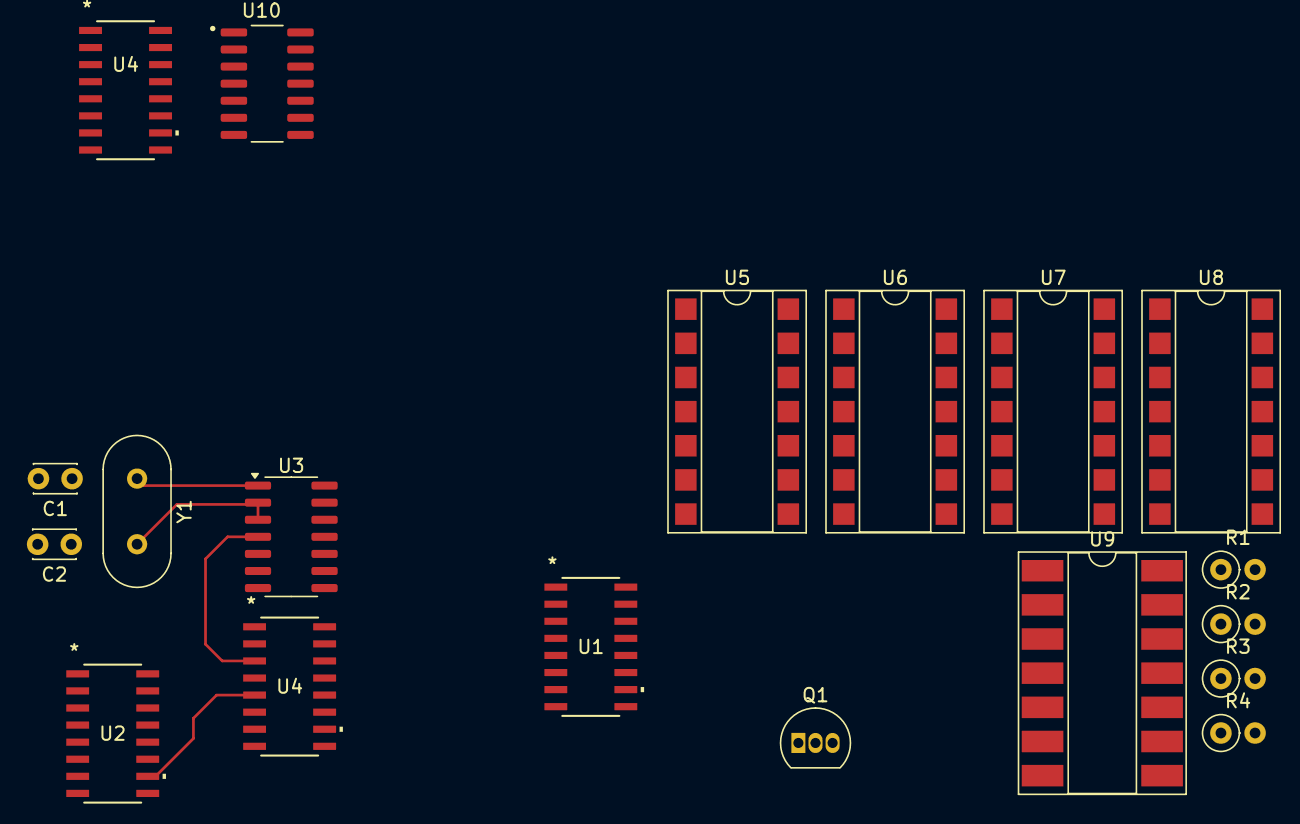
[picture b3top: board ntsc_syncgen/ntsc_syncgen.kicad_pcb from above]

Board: 2 copper layers, 19 parts (0 on the bottom side), 18 nets.

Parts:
C1, C2: 10pF; C_Disc_D3.0mm_W2.0mm_P2.50mm
Q1: PN2222A; TO-92_Inline
R1, R2, R3, R4: R; R_Axial_DIN0207_L6.3mm_D2.5mm_P2.54mm_Vertical
U1, U2: 74HC4040D; SOT109-1_NXP
U3: 74HC7014; SOIC-14_3.9x8.7mm_P1.27mm
U4, U4#2: 74HC74D; SOT109-1_NXP
U5: 74HC00; DIP-14_W7.62mm_SMDSocket_SmallPads
U6, U7, U8: 4081; DIP-14_W7.62mm_SMDSocket_SmallPads
U9: 4001; DIP-14_W8.89mm_SMDSocket_LongPads
U10: 74HC74; SOIC127P600X175-14N
Y1: Crystal; Crystal_HC49-U_Vertical

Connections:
2H: U2.6 (Q2), U7.1
4H: U2.5 (Q3), U7.2
7.1mhz_CLK1: U2.9 (Q0), U4#2.5 (1Q)
14.318mhz_CLK0: U2.10 (CP*), U3.4, U4#2.3 (1CP)
64H: U2.13 (Q7), U7.5
128H: U2.12 (Q8), U7.6
256H: U2.14 (Q9), U7.13
COMPOSITE_OUT: R3.1, R4.2
GND: C1.2, C2.2, R2.2, R3.2, U1.8 (GND), U2.8 (GND), U3.7 (GND)
H_RESET: U1.10 (CP*), U2.11 (MR)
unnamed: C1.1, U3.1, Y1.1
unnamed: C2.1, U3.2, U3.3, Y1.2
unnamed: Q1.1 (E), R4.1
unnamed: U7.3, U7.8
unnamed: U7.9, U7.11
unnamed: U7.4, U7.12
PIXEL_OUT: Q1.2 (B), R1.2, R2.1
VCC: Q1.3 (C), R1.1, U1.16 (VCC), U2.16 (VCC), U3.14 (VCC)

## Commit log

2024-10-27 example circuit
2024-12-24 more work
2025-01-26 updated project
2025-03-31 removed old version added new one
2025-04-22 lots of work
2025-07-23 added first test version
    created a small 100x100mm test version on 4 layer
